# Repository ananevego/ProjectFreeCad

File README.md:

# KiCad → FreePCB2 2.428

Конвертер библиотечных footprint-файлов KiCad `.kicad_mod` в самостоятельные
библиотеки FreePCB2 `.fpl`. Написан на Python 3.10+, внешние зависимости не нужны.

**Статус:** разработка продолжается. R_0805_2012Metric, PinHeader PTH,
MountingHole NPTH, SOT-23 и численные
регрессии проверены автоматически. Загрузка/сохранение в FreePCB2 2.428 и
физическое совмещение STL в OpenSCAD ещё требуют отдельной Windows-валидации.
Есть также синтетический контроль заполненных окружностей на обоих silk-слоях.
Добавлены legacy-дуги KiCad и контроль HC49-U (явно 2D), аудит текстов,
D_SOD-123, пакетный CLI, исходный parser УГО и минимальный writer Схематора;
добавлен сборщик связей и переносимого комплекта, окружности/дуги УГО
и профиль обычных электрических типов выводов, простой заливки и текста;
добавлены disjoint multi-unit layout, power/NC policy и straight dash/dot profile;
добавлены полный corpus workflow и проверяемая 2D preview-поставка.
Source parser читает `.kicad_sym` и старые `.lib`, сохраняя pins/units/inheritance.
Writer создаёт `.cds` для R/C/connector, составных resistor packs и физических компонентов с power pins. Проверена цепочка
symbol → footprint → существующий STL на трёх controls; GUI и физическое
совмещение 3D ещё впереди. Полная footprint-библиотека закреплена: 15 464 файла
в 155 категориях: **14 109 FPL (91,24%) с известными losses**, 1 355 явных
отказов; 542 теста проходят. Исходники и все успешные pad records проверены.
[Полный прогон, поставка и воспроизведение](docs/FULL_LIBRARY.md).
[Порядок передачи другу для Windows-проверки](docs/WINDOWS_HANDOFF.md).
[Критерии приёмки рабочего конвертера и STEP → STL-проба](docs/WORKING_CONVERTER_ACCEPTANCE.md).

## Исходные УГО KiCad

```sh
python3 -B -m src.symbol_converter KiCad/Pickit-cache.lib output/symbols/Pickit-cache.inspect.json
python3 -B -m src.symbol_converter tests/fixtures/symbols/Comparator.kicad_sym \
  output/symbols/Comparator.inspect.json --symbol LM393 --symbol LM339
```

Эти команды создают JSON исходных УГО.
Поддержаны секции/общие body styles, наследование и aliases. Конфликты pins
сохраняются с диагностикой: у PIC24 в локальном cache номера 1–16 повторены
по восемь раз, поэтому первый запуск возвращает 2 и сохраняет отчёт.
Официальные Mechanical/Comparator KiCad 9.0.0 и legacy cache проверены автоматически.
Правила: [SYMBOL_CONVERTER.md](docs/SYMBOL_CONVERTER.md).
Исследование target: [SCHEMATOR_FORMAT_RESEARCH.md](docs/SCHEMATOR_FORMAT_RESEARCH.md).

## УГО Схематора

```sh
python3 -B -m src.symbol_converter.write KiCad/Pickit-cache.lib \
  output/symbols/R_control.cds --symbol R
```

Отдельный CLI создаёт один компонент `.cds` 1.429 (CP1251) и JSON losses.
Поддержаны видимые прямые pins девяти обычных electrical types и
rectangles/polylines/circles/arcs, ограниченная foreground
заливка и literal body text, disjoint units и power terminals.
Повторяющиеся pin records, native hierarchy и неподдерживаемая графика остаются ограничениями.
Сохранены R/C/CONN_01X06 controls. Контракт ограниченного профиля проверен по
исходникам и реальной записи R3; отдельный reader проверяет emitted records.
Загрузка и connectivity в Схематоре пока не подтверждены.
Полный batch/audit **21 806 УГО** дал **12 186 CDS (55,88%) с явными losses**;
независимо проверены 249 254 вывода. Preview ZIP с reports проверен после переноса.
Собрана **массовая связанная preview-поставка: 8 210 CDS с назначенными FPL**,
878 разных корпусов и 461 существующий STL. У 6 993 найдены все model dependencies;
1 217 имеют partial/no-model. Проверены 94 540 pin/pad pairs и перенос ZIP.
[Поставка и команды](docs/MASS_COMPONENTS.md). Отдельная unlinked symbol preview
по-прежнему сохраняет `PART`.
`--pin-name-policy plain-overbar-with-loss` и `--alternate-pin-policy primary-with-loss`
передают имя без надчёркивания и основную функцию pin с явными losses; default
остаётся reject, source definitions сохраняются в JSON. [Команды и ограничения](docs/SYMBOL_BATCH.md).
Без `--footprint-name` используется placeholder `PART`; назначение имени
не подтверждает соответствие pads. `--strict` отклоняет известные layout losses.
Команды, ограничения и коды выхода: [SCHEMATOR_CONVERTER.md](docs/SCHEMATOR_CONVERTER.md).

`--curve-tolerance 0.01` задаёт mm-допуск для centerline аппроксимации curves,
включая NM rounding. Сохранены семь реальных curve controls; legacy arc
resolution учитывает explicit endpoints/swap и отдельно показывает radius/
endpoint changes. Правила: [SYMBOL_CURVES.md](docs/SYMBOL_CURVES.md).

Input/output/bidirectional/tri_state и другие обычные типы передаются как
нумерованные endpoints с явной потерей ERC; source types остаются в JSON.
Alternate pins пока отклоняются. Добавлены
пять реальных УГО и две linked chains SCR/Speaker с готовыми STL.
Профиль, отчёты и команды: [SYMBOL_ELECTRICAL.md](docs/SYMBOL_ELECTRICAL.md).

Foreground rectangles/closed simple polygons/circles покрываются straight
strokes с fill bound, default `--fill-tolerance 0.01`. Background передаётся
только как boundary с occlusion loss; modern graphic text/legacy T — как
body description с font/layout losses. Добавлены шесть real controls и две
linked chains diode/meter. [Правила и проверки](docs/SYMBOL_BODY.md).

2–16 секций с disjoint physical numbers размещаются рядом в одном native
component; independent placement/unit suffixes имеют explicit loss. Common
graphics повторяются; original common pins требуют явного режима отдельной view. `--unit-gap` default
2.54 mm; пять real controls и три array/SIP chains проверены. Native merge/
hierarchy не генерируется. [Профиль и ограничения](docs/SYMBOL_UNITS.md).

Power_in/power_out передаются как нумерованные terminals с явной потерей
power/ERC rules. No-connect по умолчанию отклоняется; явный
`--no-connect-policy connectable-with-loss` сохраняет NC как подключаемый pin
с отдельной диагностикой. Power sections LM393 и шесть real controls проверены;
три chains DIP-8/SOT-23 используют два существующих STL. Native запрет NC
не реализован. [Политика и источники](docs/SYMBOL_POWER.md).

Inverted/clock и другие pin markers переносятся отдельной body graphics.
Hidden pins default reject; `--hidden-pin-policy reveal-with-loss` раскрывает
terminals с потерей visibility/implicit global nets. Шесть real controls и
пять chains проверены. [Профиль и ограничения](docs/SYMBOL_PINS.md).

Original unit=0 pins при `--common-pin-policy common-view-with-loss`
размещаются один раз в отдельной view того же component. Четыре real networks
и три source-property SIP chains проверены; повторяющиеся source records
отклоняются. [Политика и проверки](docs/SYMBOL_COMMON.md).

## Связи и переносимый комплект

```sh
python3 -B -m src.component_converter tests/fixtures/components/control.json \
  output/components/control
python3 -B -m src.component_converter --verify output/components/control
```

Точные identifiers и pin/pad numbers проверяются до генерации и по записанным
CDS/FPL. Комплект содержит R0805/C0805/Header6 и только их существующие STL:
исходное дерево категорий и уникальные flat aliases для одной OpenSCAD папки.
SHA256 подтверждает неизменность копий; geometry/GUI/netlist не проверены.
Выход должен быть новым каталогом. Missing/ambiguous bindings остаются в manifest;
STL не конвертируются повторно. Скопированный комплект проверяется без исходников.
Правила и настройка Windows-папки: [COMPONENT_BUNDLE.md](docs/COMPONENT_BUNDLE.md).

Для проверки в целевых программах добавлен переносимый **native validation kit**:
8 bundles/24 компонента, 5 standalone FPL controls, 15 aliases существующих STL,
10 negative controls и 10 manual scenarios. Checker работает без repo и model
store; original inputs и результаты отделены. Native flags остаются false,
пока GUI/netlist/Gerber/board 3D не проверены фактически.

```sh
python3 -B -m src.native_validation output/native-validation-ready
python3 -B output/native-validation-ready/verify_kit.py
python3 -B output/native-validation-ready/verify_kit.py --init-results results/run.json
```

Для копии repo без моделей доступен `--allow-missing-models`: это явно partial
kit с `ready_for_3d_checks=false`. [Комплект, архив и протокол](docs/NATIVE_VALIDATION.md).

## Пакетная обработка

```sh
python3 -B -m src.footprint_converter.batch tests/fixtures output/batches/control --limit 7
python3 -B -m src.footprint_converter.batch tests/fixtures output/batches/control --limit 7 --resume
```

Каждый footprint получает отдельный FPL/report, стабильное имя и запись в manifest.
Ошибки изолированы; resume проверяет source/options/engine/models и хеши artifacts.
В текущей партии 6 из 7 файлов генерируются с известными потерями; старый HC49-U
получает ожидаемый отказ legacy model(at), поэтому CLI возвращает 2.
GUI и полная библиотека этим прогоном не проверены.
Подробные правила и параметры: [BATCH_CONVERTER.md](docs/BATCH_CONVERTER.md).

Средняя pinned партия: 120 footprints из 12 категорий, 110 FPL с losses и
10 явных отказов (91.67% в этой выборке). Technical mask/paste-only pads и
contact pads добавлены по source/native контракту. Новый read-only audit
проверяет source/FPL records, hashes и отдельно отмечает ambiguous numbers.
[Результаты, ограничения и команды](docs/FOOTPRINT_MEDIUM.md).
Тип stroke `default` исправлен как solid. Dash/dot/dash_dot/dash_dot_dot
для незаполненных линий/прямоугольников/простых полигонов переносятся отдельными
отрезками по фиксированному KiCad9 PCB editor profile с loss; strict отклоняет
его. Кривые и filled patterned outlines остаются отказом.
[Контракт и результаты этапа](docs/FOOTPRINT_STROKES.md).
Добавлен точный перенос custom pads, чьи anchor и прямоугольные примитивы
доказуемо образуют один центрированный прямоугольник. Slots, nonzero offsets
и непрямоугольные unions имеют структурированные причины отказа; средняя
партия остаётся 110/120. [Ограничения native pads](docs/PAD_GEOMETRY.md).

Полный корпус обрабатывается через `src.library_corpus`, batch/audit и
`src.library_release`. Поддержаны графические footprints с нулём pins;
`--description-policy ascii-escape-with-loss` явно записывает Unicode/кавычки/
control characters описания как `[U+XXXX]`, сохраняя оригинал в JSON. Номера
выводов и графические надписи этим режимом не изменяются. Default — `preserve`.
[Результаты и команды](docs/FULL_LIBRARY.md).

## Что поддерживается

| Данные KiCad | Результат |
|---|---|
| Footprints без площадок с поддержанной графикой | Контуры и `n_pins: 0`, без добавленных electrical terminals |
| Technical-only F/B.Mask/Paste SMD pads | Отдельные zero-copper/hole padstack carriers, literal aperture sizes; netlist/Gerber unverified |
| Contact pads (`connect`) | Одна внешняя copper side, mask/no paste/no hole; connector attribute имеет loss |
| Custom SMD → exact centred rectangle | До 32 rectangular gr_poly; exact union proof, source anchor сохранён, explicit aperture settings и editing/zone loss |
| SMD circle / rect / oval / roundrect | Соответствующая форма и размеры, без перестановки X/Y |
| F.Cu / B.Cu | Верхняя / нижняя площадка |
| PTH с круглым drill | Отверстие и площадки; `*.Cu` включает общий inner_pad |
| NPTH с круглым drill | Отверстие без меди; NPTH paste подавляется с диагностикой |
| Origin | Сохраняется; ось Y приводится к системе FreePCB2 |
| Centroid | Вычисляет native reader FreePCB2 по bounds площадок; без pads — по контурам |
| F.SilkS / B.SilkS | Раздельные слои 4 / 5 |
| Dwgs.User / Cmts.User | Контуры и user texts в notes=7 с диагностикой потери различия слоёв |
| Линии, незаполненные прямоугольники и полигоны | Контуры `.fpl` |
| Заполненные простые полигоны и прямоугольники | Контур и перекрывающиеся линии с ограниченным расширением, явная аппроксимация |
| Заполненные окружности | Адаптивная граница и перекрывающиеся линии; покрытие диска и ограниченная погрешность |
| Окружности, современные и legacy-дуги | Отрезки с задаваемой точностью, по умолчанию 0.01 мм; старые дуги center/start/signed angle |
| Reference / value / user texts | Параметры и тексты с явной диагностикой ограничений |
| Mask/paste margins | Pad → footprint → явные defaults; размер и скругление aperture |
| Ссылка KiCad `.3dshapes` | Поиск уже существующего STL, код OpenSCAD; без конвертации моделей |

Fab переносится в слой notes как приближение, courtyard пропускается.
Остальные custom/chamfer/trapezoid pads, настоящие slots и nonzero pad offsets, отдельные InN.Cu,
дробные углы, заполненные дуги, полигоны с отверстиями/самопересечениями,
legacy model `(at ...)` и асимметричный
paste roundrect пока не поддерживаются. Непредставимая геометрия вызывает ошибку.
Oval drill с равными осями и explicit zero offset допускаются как та же
круглая геометрия; source spelling сохраняется в JSON.
Полный контракт: [docs/FOOTPRINT_CONVERTER.md](docs/FOOTPRINT_CONVERTER.md).

## Быстрый запуск

Из корня репозитория:

```sh
python3 -B -m unittest discover -s tests -v
python3 -B src/kicad_to_freepcb_footprint.py \
  tests/fixtures/R_0805_2012Metric.kicad_mod \
  output/R_0805_2012Metric.fpl \
  --report output/R_0805_2012Metric.report.json
```

На Windows используйте `py -3` вместо `python3`; команду можно записать в одну
строку. Вход — UTF-8; `.fpl` по умолчанию — CP1251, отчёт — UTF-8 JSON.

Из корня репозитория также доступен `python3 -B -m src.footprint_converter`
с теми же аргументами. Старый скрипт можно запускать по абсолютному пути из
другого каталога; прежний Python API `convert` сохранён.

Основные тесты запускаются и в новом клоне без 3D-каталогов: они используют
временный файл только для проверки метаданных matcher, а не геометрию STL.
Отдельный интеграционный тест использует реальный R0805 STL, когда он доступен;
аналогичная проверка есть для PinHeader и SOT-23. При отсутствии моделей эти проверки
явно пропускаются. Численные unit tests продолжают работать.

В `output/` также сохранены PTH/NPTH примеры. Их параметры и воспроизводимые
команды: [малая контрольная выборка](docs/SMALL_SAMPLE_VALIDATION.md).
SOT-23 теперь преобразуется с сохранением заполненной silk-метки pin 1.
Самопересекающийся polygon вызывает ошибку и не заменяет прежний выходной файл.

Для реальной 3D-привязки положите **существующий** файл по пути:

```text
stl_files/Resistor_SMD.3dshapes/R_0805_2012Metric.stl
```

Либо укажите корень имеющегося набора через `--stl-root /path/to/stl_files`.
Без файла конвертер сгенерирует `.fpl` с `MODEL_MISSING` в отчёте, без `import`.
Он не создаёт модели и не ищет совпадение только по basename.

## Отчёт и строгий режим

`--report` сохраняет целевую ревизию, counts, исходные тексты, настройки apertures,
3D-связи и diagnostics. `loss` означает потерю информации, `assumption` —
непроверенное допущение, `approximation` — ограниченную аппроксимацию.

| Код завершения | Значение |
|---|---|
| 0 | Файл сгенерирован; возможные потери перечислены в отчёте |
| 1 | Ошибка чтения, преобразования или записи |
| 2 | `--strict` запретил результат из-за известных потерь; старый `.fpl` сохранён |

```sh
python3 -B src/kicad_to_freepcb_footprint.py input.kicad_mod output/part.fpl \
  --strict --report output/part.report.json
```

`--strict` допускает указанные в отчёте допущения и ограниченную аппроксимацию;
это не подтверждение корректности в GUI. Для текущего R0805 строгий запуск
завершится кодом 2 из-за courtyard/Fab/text. Сохранённый контрольный `.fpl`
предназначен для дальнейшей валидации, а не объявляется готовой библиотекой.

## Настройки mask/paste

Margins задаются **на сторону**, в мм; ratio — доля, например `-0.05`.
Размер paste: `X + 2*(margin + X*ratio)` и аналогично для Y.

```sh
python3 -B src/kicad_to_freepcb_footprint.py input.kicad_mod output/part.fpl \
  --default-mask-margin 0.05 \
  --default-paste-margin 0 --default-paste-ratio 0 \
  --report output/part.report.json
```

Параметры defaults должны соответствовать выбранным настройкам исходного проекта.
Pad overrides footprint; footprint overrides CLI defaults; явный ноль сохраняется.
Если обе настройки paste отсутствуют, используется FreePCB DEFAULT=99 с
диагностикой зависимости от target project. Если известна лишь одна — другая
считается нулём с диагностикой потери, запрещённой в `--strict`.
Положительный margin rect создаёт roundrect; равномерный margin roundrect
меняет радиус. Схлопнувшаяся aperture записывается как NONE.

## Тексты и 3D

Нативный `.fpl` хранит параметры reference/value, но не их actual content и
независимый слой. Значение компонента необходимо задать при размещении.
Неразрешённые `%R`/`%V`, `${REFERENCE}` и другие user text variables пропускаются с
диагностикой; исходные строки сохраняются в JSON.

```sh
python3 -B src/kicad_to_freepcb_footprint.py input.kicad_mod output/part.fpl \
  --text-variable REFERENCE=R1 --text-variable VALUE=10k
```

Такая подстановка создаёт **статический** текст. Она не создаёт динамическое поле
FreePCB2. Точное совпадение шрифта и baseline пока не обеспечено.

## Заполненные полигоны

Для `fp_poly` и `fp_rect` с `fill solid` (также `fill yes`) сохраняется исходный
контур, а внутренность покрывается перекрывающимися линиями. Native hatch не
используется. `--fill-tolerance MM` задаёт допустимое расширение записанной
геометрии, по умолчанию 0.01 мм, с учётом округления на сетку FreePCB2.
Нулевая/слишком тонкая исходная обводка расширяется в пределах этого допуска.

`fp_circle` с `fill solid`/`yes` тоже поддерживается. Исходные center/end/width
сохраняются до выбора толщины заполнения. Допуск хорды автоматически ограничен
четвертью этой толщины: так покрывается весь исходный диск, включая области вне
вписанного многоугольника. Для ненулевой исходной обводки отклонение внутрь
ограничено `--curve-tolerance`, расширение наружу — `--fill-tolerance`; общая
погрешность границы не больше максимума этих двух допусков в идеальной модели.
При допусках по умолчанию это 0.01 мм. Контрольный пример:

```sh
python3 -B -m src.footprint_converter \
  tests/fixtures/FilledCircle_Control.kicad_mod output/FilledCircle_Control.fpl \
  --report output/FilledCircle_Control.report.json
```

Это синтетический тест геометрии, без модели; `MODEL_MISSING` ожидаем.
Он не является реальным компонентом KiCad или подтверждением GUI-импорта.

Граница проверена численно **в модели круглых концов линий**. `FILL_APPROXIMATED`,
`FILL_STROKE_MODEL` и `FILL_EXPORT_UNVERIFIED` отражают аппроксимацию и ограничения.
Растеризация GUI и Gerber не проверены; минимальная толщина silk в настройках
FreePCB2 может увеличить линии. Допуск конвертера не гарантирует такой же допуск
на готовом Gerber. `--strict` допускает эту ограниченную аппроксимацию и явно
отмеченные допущения, как для существующих кривых.

Поддерживается один простой контур без отверстий, в том числе вогнутый.
Лимиты: 512 вершин на polygon/границу circle, суммарно 4096 линий заполнения
и границ на footprint. Чрезмерная детализация окружности также вызывает ошибку.
Самопересечения, самокасания и геометрия, схлопнувшаяся на целевой сетке,
вызывают ошибку. Подробности: [контракт заполнения](docs/FOOTPRINT_CONVERTER.md#заполненные-полигоны).

## Настройка и проверка 3D

STL frame по умолчанию identity с `MODEL_FRAME_UNVERIFIED`. Его можно явно задать
через `--model-translation X Y Z`, `--model-rotation X Y Z`, `--model-scale X Y Z`.
Это полное target-преобразование, заменяющее исходный model transform;
неединичные KiCad 3D transforms без явной настройки отвергаются.

Для будущей проверки R0805 в FreePCB2 2.428 выставить единицы проекта **MM** и
«Папка для Openscad» на Windows-копию `stl_files\Resistor_SMD.3dshapes`.
Загружать footprint целиком через библиотеку при добавлении детали; затем
редактировать footprint выбранной детали и сохранять `.fpl`/`.fpc`.
Меню «Импорт футпринта» добавляет геометрию группой и не проверяет полный roundtrip.

## Структура

- `src/kicad_to_freepcb_footprint.py` — совместимый Python/CLI entry point.
- `src/footprint_converter/` — реализация: `parser.py`, `model.py`,
  `geometry.py`, `format_rules.py`, `validation.py`, `model_matching.py`,
  `writer.py`, `reporting.py`, `pipeline.py`, `io.py`, `cli.py` и `errors.py`.
  Parser разбирает источник, matcher проверяет только пути и метаданные моделей,
  writer формирует строку `.fpl`; запись на диск выполняется отдельно.
- `tests/` — численные и структурные регрессии; `tests/fixtures/` — контрольный
  KiCad footprint с происхождением и лицензией KiCad Libraries.
- `output/` — контрольный `.fpl`; JSON-отчёты генерируются локально и не коммитятся,
  поскольку содержат пути конкретного компьютера.
- `FreePCB/`, `Эталон R_0805_2012Metric/` — прежние демонстрационные проекты.
- `stl_files/`, `step_files/` — ранее полученные модели, доступны отдельно
  (в том числе на Яндекс Диске), исключены из Git. Не пересоздавать их.
- STEP → STL скрипты в корне — история предыдущей конвертации;
  запускать их для использования footprint-конвертера не требуется.

[Текущий план](docs/PROJECT_PLAN.md): реализация поддержанного профиля,
полные footprint/symbol-корпуса и массовая связанная preview-поставка выполнены. Для production
нужны native-проверки и исправления по их результатам. Исключения полной партии
сохранены явно; 100% покрытия KiCad не заявляется.

Правила hide/formatting/unlocked и проверки текстов: [аудит](docs/TEXT_FIELD_AUDIT.md).

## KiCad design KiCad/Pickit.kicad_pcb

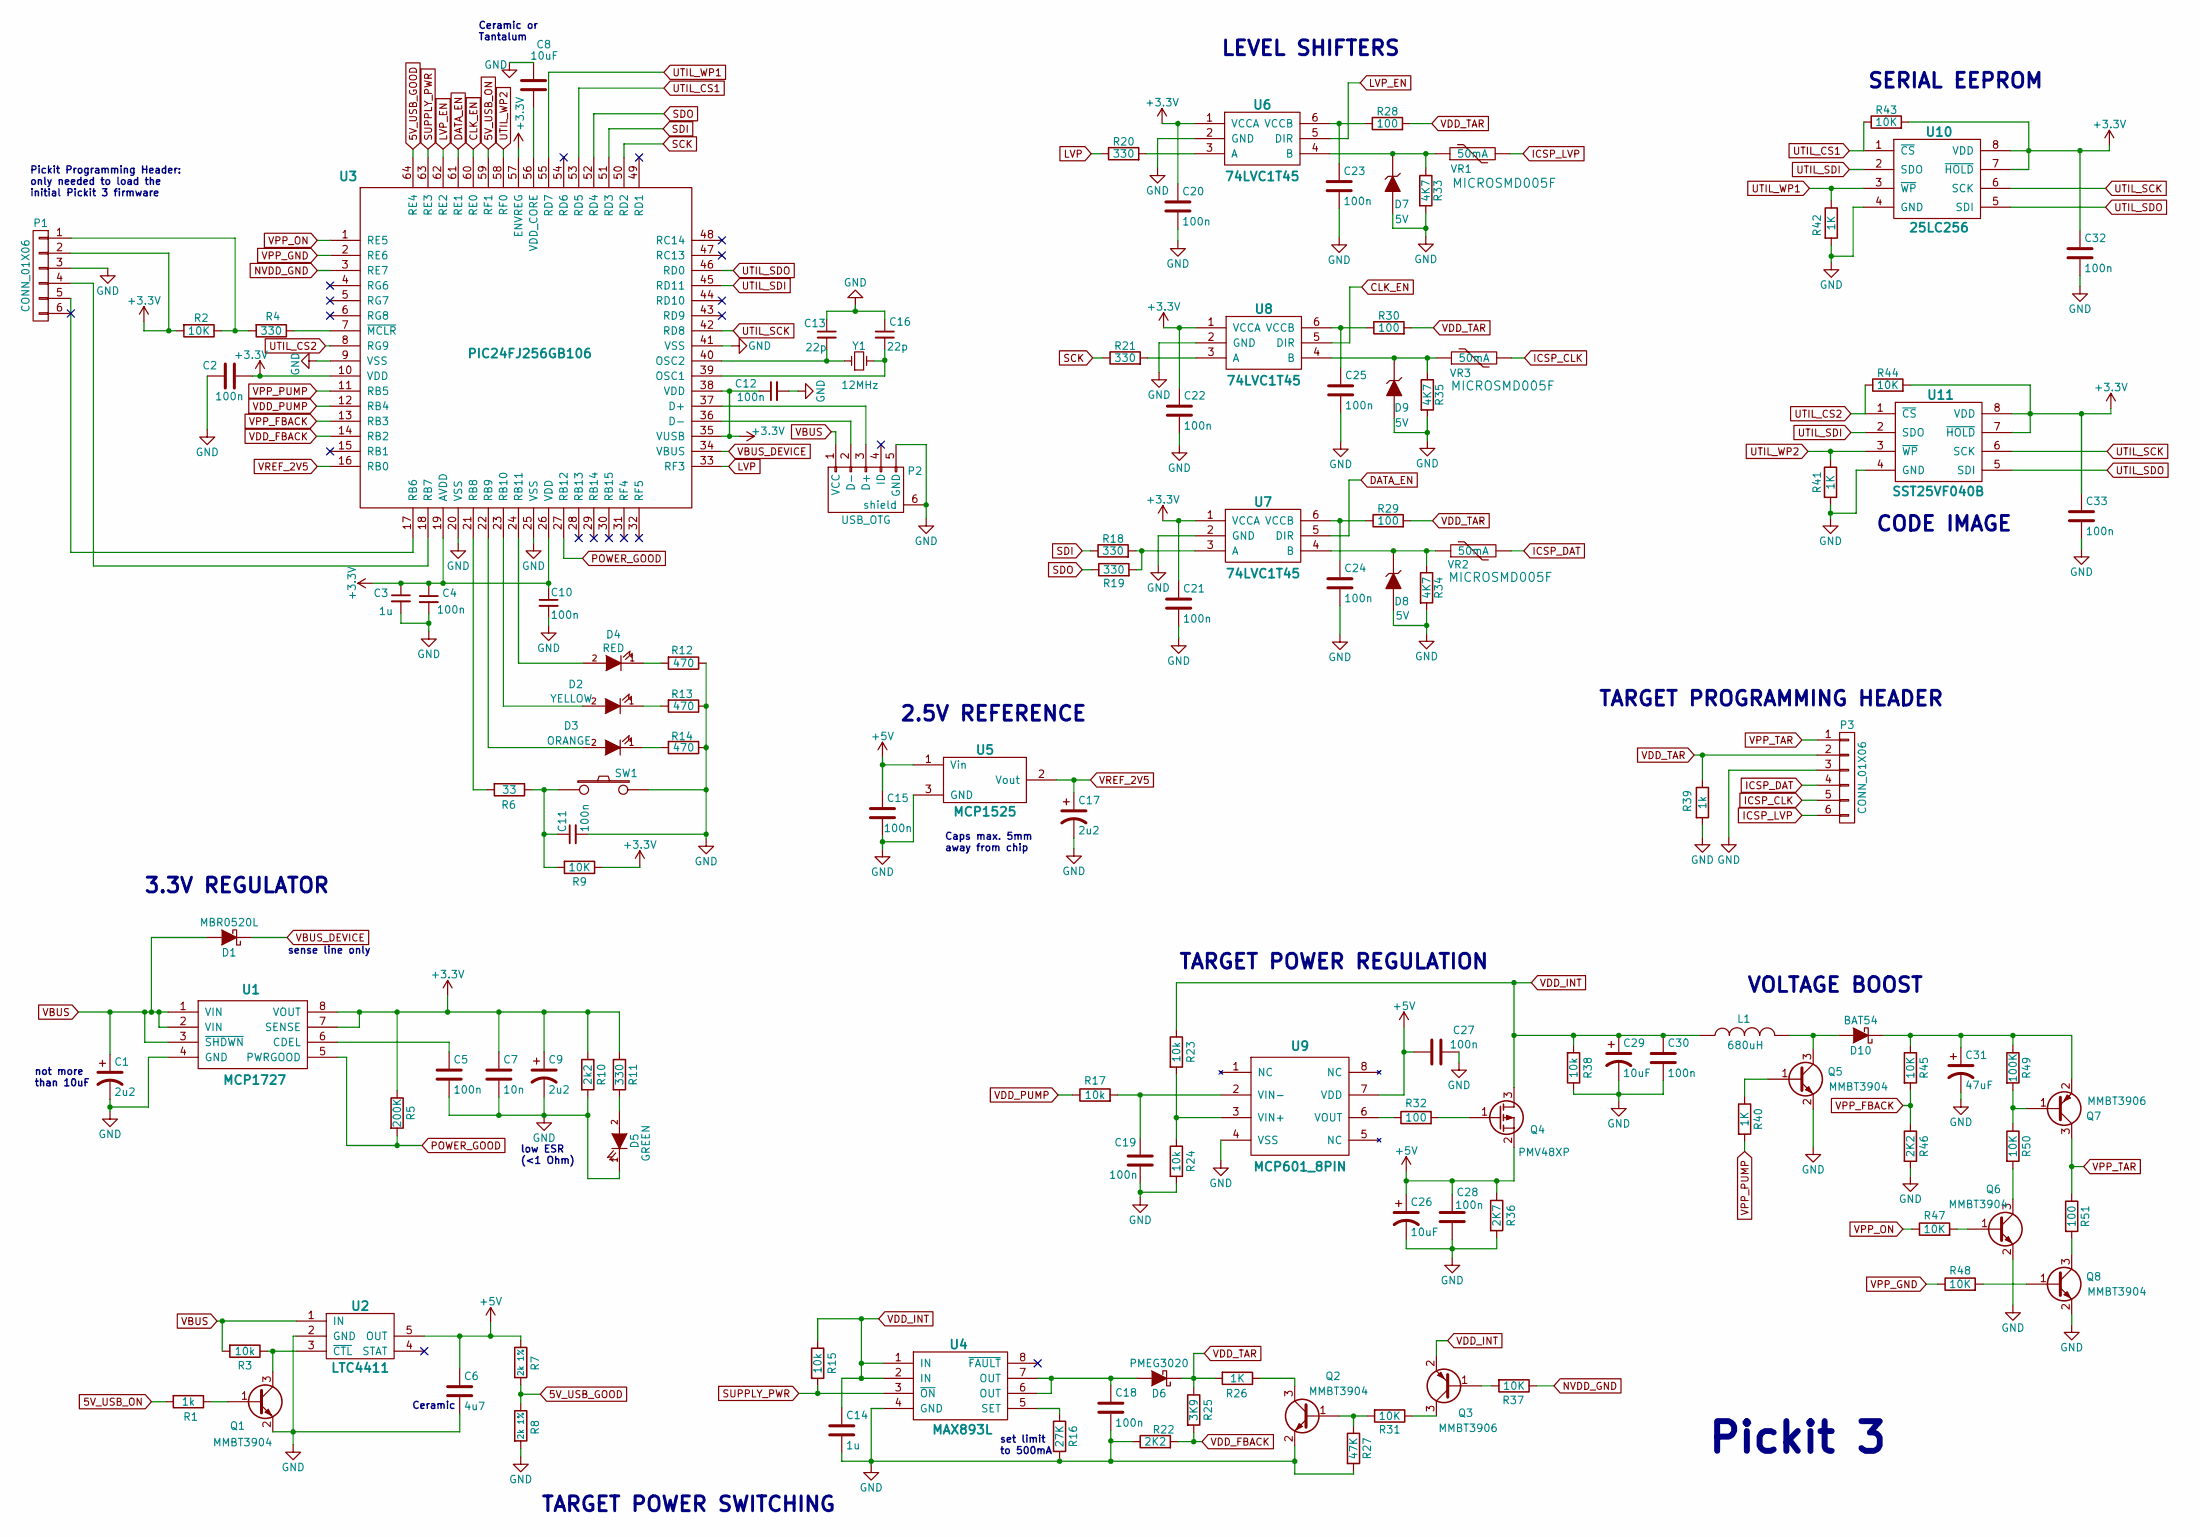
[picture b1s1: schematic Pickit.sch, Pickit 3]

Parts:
C1, C17: 2u2; TantalC_SizeC_EIA-6032_HandSoldering
C2, C4, C5, C10, C11, C12, C15, C18, C19, C20, C21, C22, C23, C24, C25, C27, C28, C30, C32, C33: 100n; C_0805_HandSoldering
C3, C14: 1u; C_0805_HandSoldering
C6: 4u7; C_0805_HandSoldering
C7: 10n; C_0805_HandSoldering
C8, C26, C29: 10uF; TantalC_SizeC_EIA-6032_HandSoldering
C9: 2u2; TantalC_SizeB_EIA-3528_HandSoldering
C13, C16: 22p; C_0805_HandSoldering
C31: 47uF; TantalC_SizeD_EIA-7343_HandSoldering
D1: MBR0520L; SOD-123
D2: YELLOW; LED-0805
D3: ORANGE; LED-0805
D4: RED; LED-0805
D5: GREEN; LED-0805
D6: PMEG3020; SOD-123
D7, D8, D9: 5V; SOD-123
D10: BAT54; SOD-123
L1: 680uH; R_1210_HandSoldering
P1, P3: CONN_01X06; Pin_Header_Straight_1x06
P2: USB_OTG; USB_Mini-B
Q1, Q2, Q5, Q6, Q8: MMBT3904; SOT-23_Handsoldering
Q3, Q7: MMBT3906; SOT-23_Handsoldering
Q4: PMV48XP; SOT-23_Handsoldering
R1, R39: 1k; R_0805_HandSoldering
R2, R9, R31, R37, R43, R44, R45, R47, R48, R50: 10K; R_0805_HandSoldering
R3, R15, R17, R23, R24, R38: 10k; R_0805_HandSoldering
R4, R11, R18, R19, R20, R21: 330; R_0805_HandSoldering
R5: 200K; R_0805_HandSoldering
R6: 33; R_0805_HandSoldering
R7, R8: 2k 1%; R_0805_HandSoldering
R10: 2k2; R_0805_HandSoldering
R12, R13, R14: 470; R_0805_HandSoldering
R16: 27K; R_0805_HandSoldering
R22, R46: 2K2; R_0805_HandSoldering
R25: 3K9; R_0805_HandSoldering
R26, R40, R41, R42: 1K; R_0805_HandSoldering
R27: 47K; R_0805_HandSoldering
R28, R29, R30, R32, R51: 100; R_0805_HandSoldering
R33, R34, R35: 4K7; R_0805_HandSoldering
R36: 2K7; R_0805_HandSoldering
R49: 100K; R_0805_HandSoldering
SW1: SW_PUSH; SW_SPST_PTS645
U1: MCP1727; SOIC-8_3.9x4.9mm_Pitch1.27mm
U2: LTC4411; SOT-23-5
U3: PIC24FJ256GB106; TQFP-64_10x10mm_Pitch0.5mm
U4: MAX893L; SOIC-8_3.9x4.9mm_Pitch1.27mm
U5: MCP1525; SOT-23_Handsoldering
U6, U7, U8: 74LVC1T45; SOT-23-6
U9: MCP601_8PIN; SOIC-8_3.9x4.9mm_Pitch1.27mm
U10: 25LC256; SOIC-8_3.9x4.9mm_Pitch1.27mm
U11: SST25VF040B; SOIC-8_3.9x4.9mm_Pitch1.27mm
VR1, VR2, VR3: 50mA; R_1210_HandSoldering; Part MICROSMD005F
Y1: 12MHz; Crystal_HC49-SD_SMD

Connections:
5V_USB_GOOD: R7.2, R8.1, U3.64 (RE4)
5V_USB_ON: R1.2, U3.59 (RF1)
+3V3: C2.2, C3.1, C4.1, C7.1, C9.1, C10.1, C12.1, C20.1, C21.1, C22.1, C32.1, C33.1, P1.2, R2.2, R5.1, R9.1, R10.1, R11.1, R43.2, R44.2, U1.7 (SENSE), U1.8 (VOUT), U3.10 (VDD), U3.19 (AVDD), U3.26 (VDD), U3.35 (VUSB), U3.38 (VDD), U3.57 (ENVREG), U6.1 (VCCA), U7.1 (VCCA), U8.1 (VCCA), U10.7 (~HOLD), U10.8 (VDD), U11.7 (~HOLD), U11.8 (VDD)
+5V: C6.1, C15.1, C26.1, C27.2, C28.1, Q4.2 (S), R7.1, R36.1, U2.5 (OUT), U5.1 (Vin), U9.7 (VDD)
CLK_EN: U3.60 (RE0), U8.5 (DIR)
DATA_EN: U3.61 (RE1), U7.5 (DIR)
GND: C1.2, C2.1, C3.2, C4.2, C5.2, C6.2, C7.2, C8.1, C9.2, C10.2, C11.2, C12.2, C13.1, C14.2, C15.2, C16.1, C17.2, C18.2, C19.2, C20.2, C21.2, C22.2, C23.2, C24.2, C25.2, C26.2, C27.1, C28.2, C29.2, C30.2, C31.2, C32.2, C33.2, D5.1 (K), D7.2 (A), D8.2 (A), D9.2 (A), P1.3, P2.5 (GND), P2.6 (shield), P3.3, Q1.2 (E), Q2.2 (E), Q5.2 (E), Q6.2 (E), Q8.2 (E), R8.2, R10.2, R12.1, R13.1, R14.1, R16.2, R22.1, R24.2, R27.2, R33.2, R34.2, R35.2, R36.2, R38.1, R39.2, R41.2, R42.2, R46.2, SW1.2, U1.4 (GND), U2.2 (GND), U3.9 (VSS), U3.20 (VSS), U3.25 (VSS), U3.41 (VSS), U4.4 (GND), U5.3 (GND), U6.2 (GND), U7.2 (GND), U8.2 (GND), U9.4 (VSS), U10.4 (GND), U11.4 (GND)
ICSP_CLK: P3.5, VR3.2
ICSP_DAT: P3.4, VR2.2
ICSP_LVP: P3.6, VR1.2
LVP: R20.1, U3.33 (RF3)
LVP_EN: U3.62 (RE2), U6.5 (DIR)
NVDD_GND: R37.1, U3.3 (RE7)
unnamed: C5.1, U1.6 (CDEL)
unnamed: C8.2, U3.56 (VDD_CORE)
unnamed: C11.1, R6.1, R9.2, SW1.1
unnamed: C13.2, U3.40 (OSC2), Y1.1
unnamed: C16.2, U3.39 (OSC1), Y1.2
unnamed: C18.1, D6.2 (A), U4.6 (OUT), U4.7 (OUT)
unnamed: C19.1, R17.2, U9.2 (VIN-)
unnamed: C23.1, R28.1, U6.6 (VCCB)
unnamed: C24.1, R29.1, U7.6 (VCCB)
unnamed: C25.1, R30.1, U8.6 (VCCB)
unnamed: C31.1, D10.1 (K), Q7.2 (E), R45.1, R49.1
unnamed: D2.1 (K), R13.2
unnamed: D2.2 (A), U3.23 (RB10)
unnamed: D3.1 (K), R14.2
unnamed: D3.2 (A), U3.22 (RB9)
unnamed: D4.1 (K), R12.2
unnamed: D4.2 (A), U3.24 (RB11)
unnamed: D5.2 (A), R11.2
unnamed: D7.1 (K), R33.1, U6.4 (B), VR1.1
unnamed: D8.1 (K), R34.1, U7.4 (B), VR2.1
unnamed: D9.1 (K), R35.1, U8.4 (B), VR3.1
unnamed: D10.2 (A), L1.2, Q5.3 (C)
unnamed: P1.1, R2.1, R4.2
unnamed: P1.4, U3.18 (RB7)
unnamed: P1.5, U3.17 (RB6)
unnamed: P2.2 (D-), U3.36 (D-)
unnamed: P2.3 (D+), U3.37 (D+)
unnamed: Q1.1 (B), R1.1
unnamed: Q1.3 (C), R3.1, U2.3 (~CTL)
unnamed: Q2.1 (B), R27.1, R31.2
unnamed: Q2.3 (C), R26.1
unnamed: Q3.1 (B), R37.2
unnamed: Q3.3 (C), R31.1
unnamed: Q4.1 (G), R32.2
unnamed: Q5.1 (B), R40.1
unnamed: Q6.1 (B), R47.2
unnamed: Q6.3 (C), R50.2
unnamed: Q7.1 (B), R49.2, R50.1
unnamed: Q8.1 (B), R48.2
unnamed: Q8.3 (C), R51.2
unnamed: R4.1, U3.7 (~MCLR)
unnamed: R6.2, U3.21 (RB8)
unnamed: R16.1, U4.5 (SET)
unnamed: R18.2, R19.2, U7.3 (A)
unnamed: R20.2, U6.3 (A)
unnamed: R21.2, U8.3 (A)
unnamed: R23.2, R24.1, U9.3 (VIN+)
unnamed: R32.1, U9.6 (VOUT)
POWER_GOOD: R5.2, U1.5 (PWRGOOD), U3.27 (RB12)
SCK: R21.1, U3.50 (RD2)
SDI: R18.1, U3.51 (RD3)
SDO: R19.1, U3.52 (RD4)
SUPPLY_PWR: R15.2, U3.63 (RE3), U4.3 (~ON)
UTIL_CS1: R43.1, U3.53 (RD5), U10.1 (~CS)
UTIL_CS2: R44.1, U3.8 (RG9), U11.1 (~CS)
UTIL_SCK: U3.42 (RD8), U10.6 (SCK), U11.6 (SCK)
UTIL_SDI: U3.45 (RD11), U10.2 (SDO), U11.2 (SDO)
UTIL_SDO: U3.46 (RD0), U10.5 (SDI), U11.5 (SDI)
UTIL_WP1: R42.1, U3.55 (RD7), U10.3 (~WP)
UTIL_WP2: R41.1, U3.58 (RF0), U11.3 (~WP)
VBUS: C1.1, D1.2 (A), P2.1 (VCC), R3.2, U1.1 (VIN), U1.2 (VIN), U1.3 (~SHDWN), U2.1 (IN)
VBUS_DEVICE: D1.1 (K), U3.34 (VBUS)
VDD_FBACK: R22.2, R25.2, U3.14 (RB2)
VDD_INT: C14.1, C29.1, C30.1, L1.1, Q3.2 (E), Q4.3 (D), R15.1, R23.1, R38.2, U4.1 (IN), U4.2 (IN)
VDD_PUMP: R17.1, U3.12 (RB4)
VDD_TAR: D6.1 (K), P3.2, R25.1, R26.2, R28.2, R29.2, R30.2, R39.1
VPP_FBACK: R45.2, R46.1, U3.13 (RB3)
VPP_GND: R48.1, U3.2 (RE6)
VPP_ON: R47.1, U3.1 (RE5)
VPP_PUMP: R40.2, U3.11 (RB5)
VPP_TAR: P3.1, Q7.3 (C), R51.1
VREF_2V5: C17.1, U3.16 (RB0), U5.2 (Vout)

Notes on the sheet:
SERIAL EEPROM
CODE IMAGE
TARGET PROGRAMMING HEADER
VOLTAGE BOOST
LEVEL SHIFTERS
2.5V REFERENCE
3.3V REGULATOR
TARGET POWER SWITCHING
TARGET POWER REGULATION
Caps max. 5mm away from chip
low ESR (<1 Ohm)
not more than 10uF
Ceramic or Tantalum
set limit to 500mA
sense line only
Ceramic
Pickit Programming Header: only needed to load the initial Pickit 3 firmware
Pickit 3

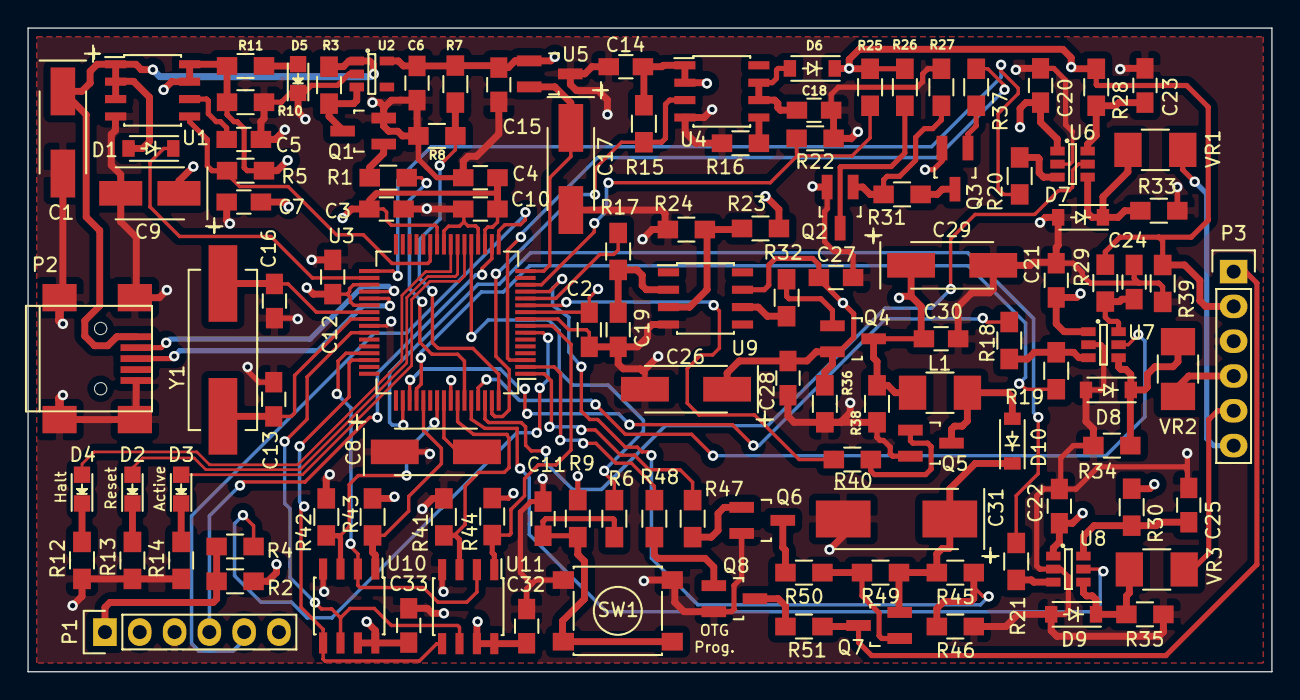
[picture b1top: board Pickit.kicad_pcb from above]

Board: 4 copper layers, 90.8 x 47.0 mm, 122 parts (0 on the bottom side), 85 nets.

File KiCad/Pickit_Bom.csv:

Reference, Value,Part,Footprint,,Notes,
R6,33,311-33.0CRCT-ND,R_0805_HandSoldering,,,
R28,100,311-100CRCT-ND,R_0805_HandSoldering,,,
R29,100,311-100CRCT-ND,R_0805_HandSoldering,,,
R30,100,311-100CRCT-ND,R_0805_HandSoldering,,,
R32,100,311-100CRCT-ND,R_0805_HandSoldering,,,
R51,100,311-100CRCT-ND,R_0805_HandSoldering,,,
R11,330,311-330CRCT-ND,R_0805_HandSoldering,,,
R18,330,311-330CRCT-ND,R_0805_HandSoldering,,,
R19,330,311-330CRCT-ND,R_0805_HandSoldering,,,
R20,330,311-330CRCT-ND,R_0805_HandSoldering,,,
R21,330,311-330CRCT-ND,R_0805_HandSoldering,,,
R4,330,311-330CRCT-ND,R_0805_HandSoldering,,,
R12,470,311-470CRCT-ND,R_0805_HandSoldering,,,
R13,470,311-470CRCT-ND,R_0805_HandSoldering,,,
R14,470,311-470CRCT-ND,R_0805_HandSoldering,,,
R49,100K,311-100KCRCT-ND,R_0805_HandSoldering,,,
C10,100n,1276-1003-1-ND,C_0805_HandSoldering,,,
C11,100n,1276-1003-1-ND,C_0805_HandSoldering,,,
C12,100n,1276-1003-1-ND,C_0805_HandSoldering,,,
C15,100n,1276-1003-1-ND,C_0805_HandSoldering,,,
C18,100n,1276-1003-1-ND,C_0805_HandSoldering,,,
C19,100n,1276-1003-1-ND,C_0805_HandSoldering,,,
C2,100n,1276-1003-1-ND,C_0805_HandSoldering,,,
C20,100n,1276-1003-1-ND,C_0805_HandSoldering,,,
C21,100n,1276-1003-1-ND,C_0805_HandSoldering,,,
C22,100n,1276-1003-1-ND,C_0805_HandSoldering,,,
C23,100n,1276-1003-1-ND,C_0805_HandSoldering,,,
C24,100n,1276-1003-1-ND,C_0805_HandSoldering,,,
C25,100n,1276-1003-1-ND,C_0805_HandSoldering,,,
C27,100n,1276-1003-1-ND,C_0805_HandSoldering,,,
C28,100n,1276-1003-1-ND,C_0805_HandSoldering,,,
C30,100n,1276-1003-1-ND,C_0805_HandSoldering,,,
C32,100n,1276-1003-1-ND,C_0805_HandSoldering,,,
C33,100n,1276-1003-1-ND,C_0805_HandSoldering,,,
C4,100n,1276-1003-1-ND,C_0805_HandSoldering,,,
C5,100n,1276-1003-1-ND,C_0805_HandSoldering,,,
R15,10k,311-10.0KCRCT-ND,R_0805_HandSoldering,,,
R17,10k,311-10.0KCRCT-ND,R_0805_HandSoldering,,,
R2,10K,311-10.0KCRCT-ND,R_0805_HandSoldering,,,
R23,10k,311-10.0KCRCT-ND,R_0805_HandSoldering,,,
R24,10k,311-10.0KCRCT-ND,R_0805_HandSoldering,,,
R3,10k,311-10.0KCRCT-ND,R_0805_HandSoldering,,,
R31,10K,311-10.0KCRCT-ND,R_0805_HandSoldering,,,
R37,10K,311-10.0KCRCT-ND,R_0805_HandSoldering,,,
R38,10k,311-10.0KCRCT-ND,R_0805_HandSoldering,,,
R43,10K,311-10.0KCRCT-ND,R_0805_HandSoldering,,,
R44,10K,311-10.0KCRCT-ND,R_0805_HandSoldering,,,
R45,10K,311-10.0KCRCT-ND,R_0805_HandSoldering,,,
R47,10K,311-10.0KCRCT-ND,R_0805_HandSoldering,,,
R48,10K,311-10.0KCRCT-ND,R_0805_HandSoldering,,,
R50,10K,311-10.0KCRCT-ND,R_0805_HandSoldering,,,
R9,10K,311-10.0KCRCT-ND,R_0805_HandSoldering,,,
C7,10n,1276-2434-1-ND,C_0805_HandSoldering,,,
C26,10uF,399-8333-1-ND,TantalC_SizeC_EIA-6032,,tantalum,
C29,10uF,399-8333-1-ND,TantalC_SizeC_EIA-6032,,tantalum,
C8,10uF,399-8333-1-ND,TantalC_SizeC_EIA-6032,,tantalum,
Y1,12MHz,XC1770CT-ND,Crystal_HC49-SD_SMD,,,
R1,1k,311-1.00KCRCT-ND,R_0805_HandSoldering,,,
R26,1K,311-1.00KCRCT-ND,R_0805_HandSoldering,,,
R39,1k,311-1.00KCRCT-ND,R_0805_HandSoldering,,,
R40,1K,311-1.00KCRCT-ND,R_0805_HandSoldering,,,
R41,1K,311-1.00KCRCT-ND,R_0805_HandSoldering,,,
R42,1K,311-1.00KCRCT-ND,R_0805_HandSoldering,,,
C14,1u,1276-2926-1-ND,C_0805_HandSoldering,,,
C3,1u,1276-2926-1-ND,C_0805_HandSoldering,,,
R5,200K,311-200KCRCT-ND,R_0805_HandSoldering,,,
C13,22p,399-9190-1-ND,C_0805_HandSoldering,,,
C16,22p,399-9190-1-ND,C_0805_HandSoldering,,,
U10,25LC256,25LC256-I/SN-ND,SOIC-8_3.9 x 4.9,,,
R16,27K,311-27.0KCRCT-ND,R_0805_HandSoldering,,,
R7,2k 1%,311-2.00KCRCT-ND,R_0805_HandSoldering,,,
R8,2k 1%,311-2.00KCRCT-ND,R_0805_HandSoldering,,,
R10,2k2,311-2.20KCRCT-ND,R_0805_HandSoldering,,,
R22,2K2,311-2.20KCRCT-ND,R_0805_HandSoldering,,,
R46,2K2,311-2.20KCRCT-ND,R_0805_HandSoldering,,,
R36,2K7,311-2.70KCRCT-ND,R_0805_HandSoldering,,,
C1,2u2,399-3740-1-ND,TantalC_SizeC_EIA-6032,,tantalum,
C17,2u2,399-3740-1-ND,TantalC_SizeC_EIA-6032,,tantalum,
C9,2u2,478-9061-1-ND,TantalC_SizeB_EIA-3528,,tantalum,< 1 Ohm
R25,3K9,311-3.90KCRCT-ND,R_0805_HandSoldering,,,
R27,47K,311-47.0KCRCT-ND,R_0805_HandSoldering,,,
C31,47uF,399-3905-1-ND,TantalC_SizeD_EIA-7343,,tantalum,
R33,4K7,YAG1325CT-ND,R_0805_HandSoldering,,,
R34,4K7,YAG1325CT-ND,R_0805_HandSoldering,,,
R35,4K7,YAG1325CT-ND,R_0805_HandSoldering,,,
C6,4u7,1276-2972-1-ND,C_0805_HandSoldering,,ceramic,
VR1,50mA,MICROSMD005FCT-ND,R_1210_HandSoldering,MICROSMD005F,,
VR2,50mA,MICROSMD005FCT-ND,R_1210_HandSoldering,MICROSMD005F,,
VR3,50mA,MICROSMD005FCT-ND,R_1210_HandSoldering,MICROSMD005F,,
D7,5V Zener,568-6370-1-ND,SOD-123,,,
D8,5V Zener,568-6370-1-ND,SOD-123,,,
D9,5V Zener,568-6370-1-ND,SOD-123,,,
L1,680uH,495-2654-1-ND,R_1210_HandSoldering,,,
U6,74LVC1T45,296-16843-1-ND,SOT-23-6,,,
U7,74LVC1T45,296-16843-1-ND,SOT-23-6,,,
U8,74LVC1T45,296-16843-1-ND,SOT-23-6,,,
D10,BAT54,BAT54T1GOSCT-ND,SOD-123,,,
D3,BLUE (Orange),732-4982-1-ND,LED-0805,,,
P1,CONN_01X06,,Pin_Header_Straight_1x06,,,
P3,CONN_01X06,,Pin_Header_Straight_1x06,,,
D5,GREEN,732-4986-1-ND,LED-0805,,,
U2,LTC4411,LTC4411ES5#TRMPBFCT-ND,SOT-23-5,,,
U4,MAX893L,MAX893LESA+-ND,SOIC-8_3.9 x 4.9,,,
D1,MBR0520L,MBR0520LT1GOSCT-ND,SOD-123,,,
U5,MCP1525,MCP1525T-I/TTCT-ND,SOT-23,,,
U1,MCP1727,MCP1727-3302E/SN-ND,SOIC-8_3.9 x 4.9,,,
U9,MCP601_8PIN,MCP601-I/SN-ND,SOIC-8_3.9 x 4.9,,,
Q1,MMBT3904,MMBT3904FSCT-ND,SOT-23_HandSoldering,,,
Q2,MMBT3904,MMBT3904FSCT-ND,SOT-23_HandSoldering,,,
Q5,MMBT3904,MMBT3904FSCT-ND,SOT-23_HandSoldering,,,
Q6,MMBT3904,MMBT3904FSCT-ND,SOT-23_HandSoldering,,,
Q8,MMBT3904,MMBT3904FSCT-ND,SOT-23_HandSoldering,,,
Q3,MMBT3906,MMBT3906FSCT-ND,SOT-23_HandSoldering,,,
Q7,MMBT3906,MMBT3906FSCT-ND,SOT-23_HandSoldering,,,
U3,PIC24FJ256GB106,PIC24FJ256GB106-I/PT-ND,TQFP-64_10x10mm_Pitch0.5mm,,,
D6,PMEG3020,568-4129-1-ND,SOD-123,,,
Q4,PMV48XP,568-7579-1-ND,SOT-23_HandSoldering,,,
D4,RED,732-4984-1-ND,LED-0805,,,
U11,SST25VF040B,SST25VF040B-50-4I-SAF-ND,SOIC-8_3.9 x 4.9,,,
SW1,SW_PUSH,CKN9087CT-ND,SW_SPST_PTS645,,,
P2,USB_OTG,609-4700-1-ND,USB_Mini-B,,,
D2,YELLOW,732-4987-1-ND,LED-0805,,,
